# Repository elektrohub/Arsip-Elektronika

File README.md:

# Arsip Elektronika
 
Arsip arsip hobi yang diremajakan ulang (update), disalin ke dalam format Eagle-Cad 7.x, difabrikasi 
[di Elecrow](https://www.elecrow.com)

Semua skematik dan pcb 100% jalan

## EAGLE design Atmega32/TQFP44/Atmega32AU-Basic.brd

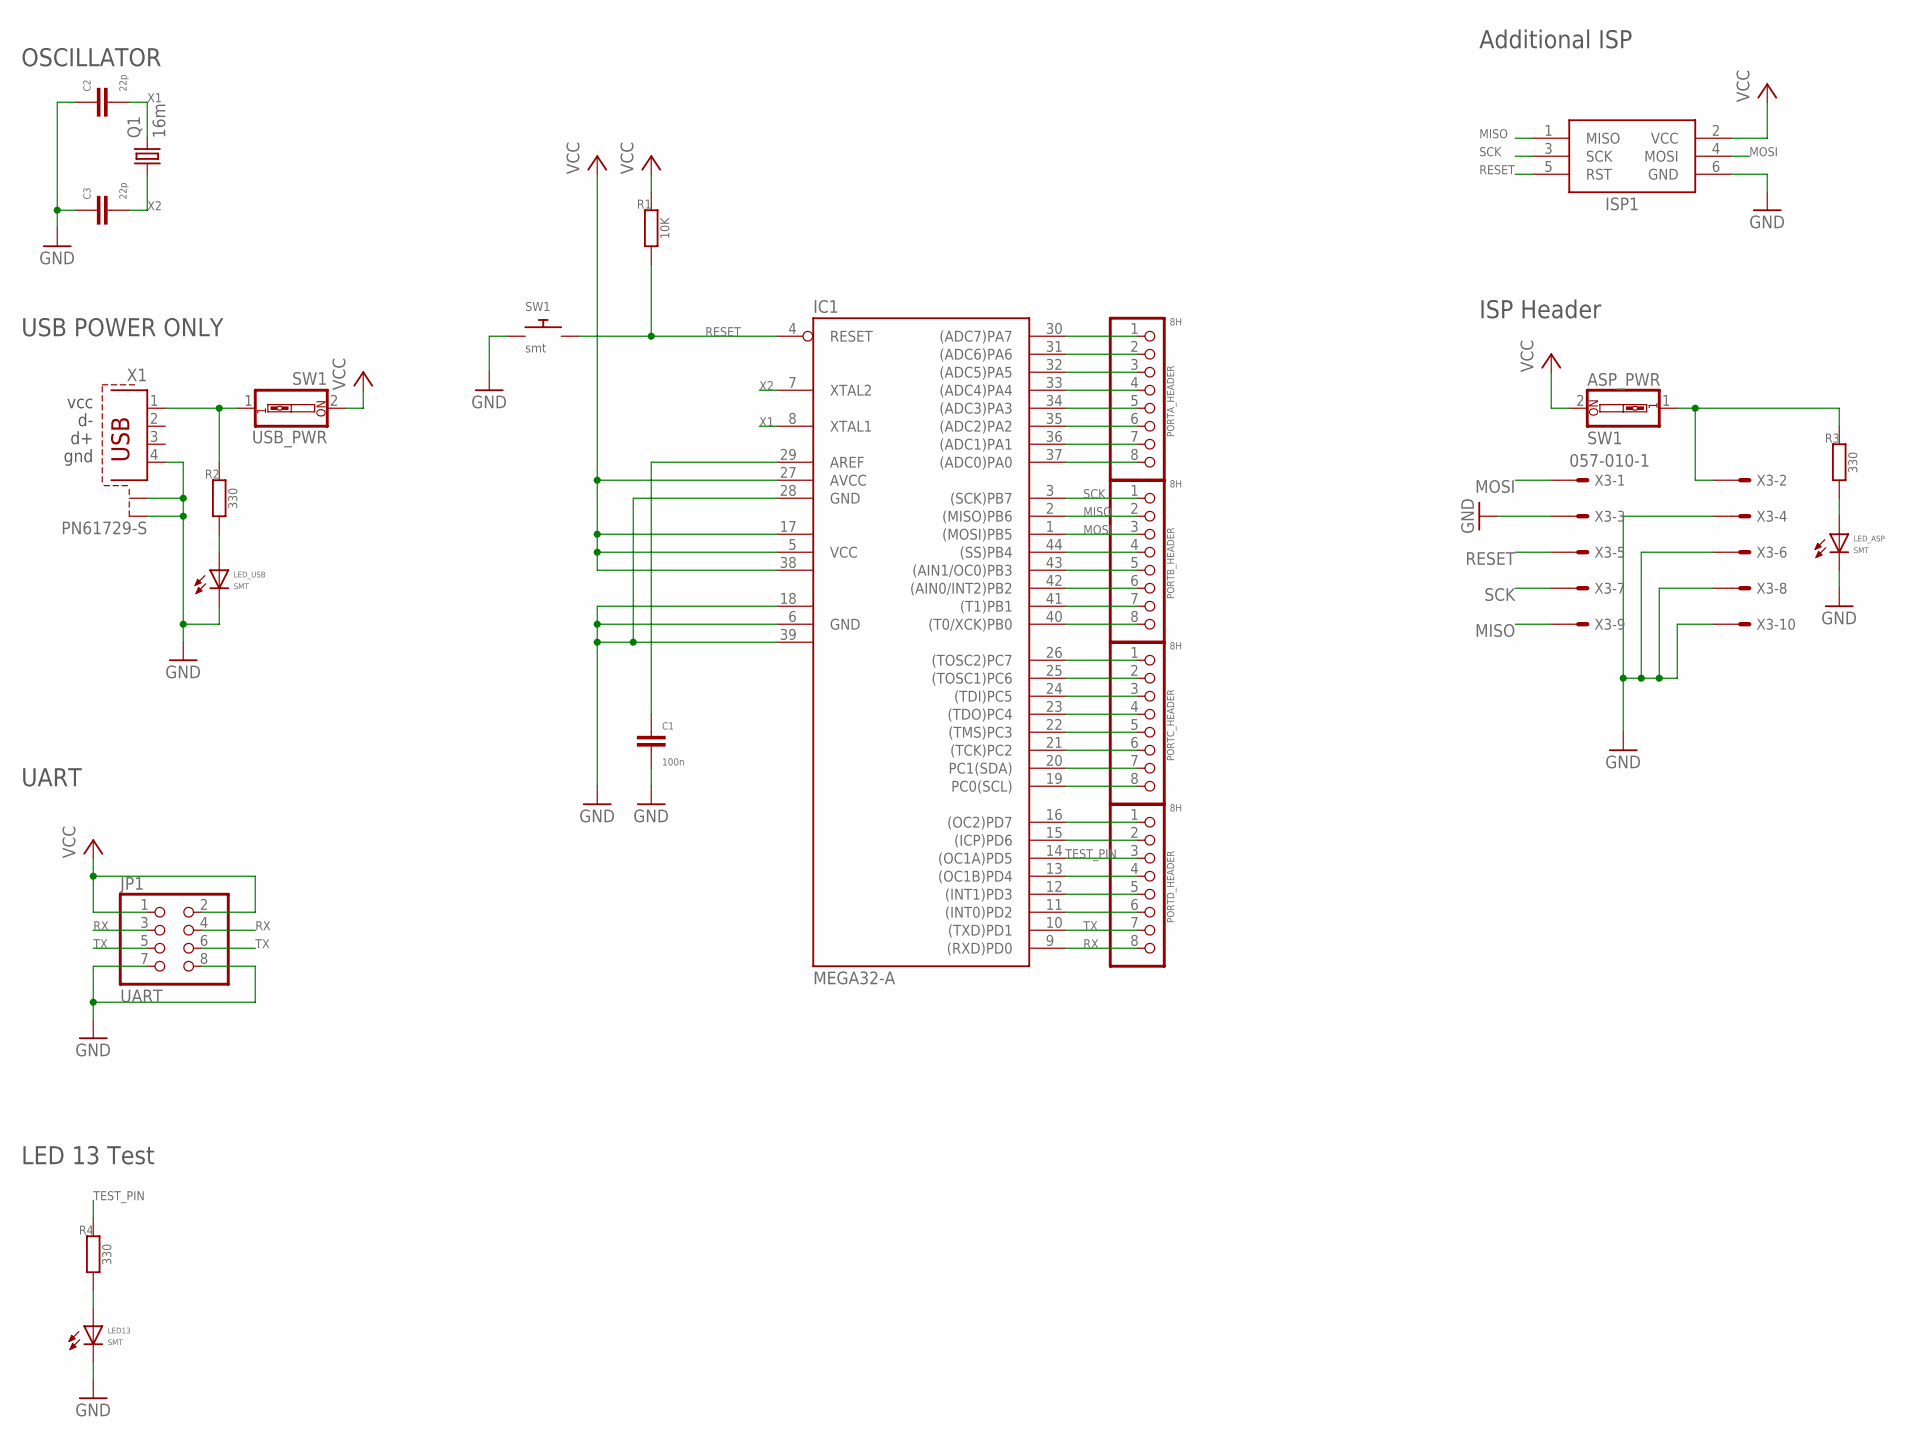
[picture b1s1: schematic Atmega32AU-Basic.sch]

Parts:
ASP_PWR: SW1; EDG-01
C1: 100n; C1206
C2, C3: 22p; C1206
IC1: MEGA32-A; TQFP44
ISP1: AVRISP-6; AVRISP
JP1: UART; 2X04
LED13: SMT; 1206
LED_ASP: SMT; 1206
LED_USB: SMT; 1206
PORTA_HEADER: 8H; 1X08-BIG
PORTB_HEADER: 8H; 1X08-BIG
PORTC_HEADER: 8H; 1X08-BIG
PORTD_HEADER: 8H; 1X08-BIG
Q1: 16m; HC49UP
R1: 10K; M1206
R2, R3, R4: 330; M1206
SW1: smt; TACT_PANA-EVQ
USB_PWR: SW1; EDG-01
X1: PN61729-S
X3: 057-010-1

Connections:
GND: C1.2, C2.1, C3.1, IC1.6 (GND), IC1.18 (GND1), IC1.28 (GND), IC1.39 (GND2), ISP1.6 (GND), JP1.7, JP1.8, LED13.C, LED_ASP.C, LED_USB.C, SW1.P$1, X1.4, X1.S1, X1.S2, X3.3, X3.4, X3.6, X3.8, X3.10
MISO: IC1.2 ((MISO)PB6), ISP1.1 (MISO), PORTB_HEADER.2, X3.9
MOSI: IC1.1 ((MOSI)PB5), ISP1.4 (MOSI), PORTB_HEADER.3, X3.1
unnamed: C1.1, IC1.29 (AREF)
unnamed: IC1.30 ((ADC7)PA7), PORTA_HEADER.1
unnamed: IC1.31 ((ADC6)PA6), PORTA_HEADER.2
unnamed: IC1.32 ((ADC5)PA5), PORTA_HEADER.3
unnamed: IC1.33 ((ADC4)PA4), PORTA_HEADER.4
unnamed: IC1.34 ((ADC3)PA3), PORTA_HEADER.5
unnamed: IC1.35 ((ADC2)PA2), PORTA_HEADER.6
unnamed: IC1.36 ((ADC1)PA1), PORTA_HEADER.7
unnamed: R2.2, USB_PWR.1, X1.1
unnamed: ASP_PWR.1, R3.2, X3.2
unnamed: LED_USB.A, R2.1
unnamed: LED13.A, R4.1
unnamed: IC1.44 ((SS)PB4), PORTB_HEADER.4
unnamed: IC1.43 ((AIN1/OC0)PB3), PORTB_HEADER.5
unnamed: IC1.42 ((AIN0/INT2)PB2), PORTB_HEADER.6
unnamed: IC1.41 ((T1)PB1), PORTB_HEADER.7
unnamed: LED_ASP.A, R3.1
unnamed: IC1.26 ((TOSC2)PC7), PORTC_HEADER.1
unnamed: IC1.25 ((TOSC1)PC6), PORTC_HEADER.2
unnamed: IC1.24 ((TDI)PC5), PORTC_HEADER.3
unnamed: IC1.23 ((TDO)PC4), PORTC_HEADER.4
unnamed: IC1.22 ((TMS)PC3), PORTC_HEADER.5
unnamed: IC1.21 ((TCK)PC2), PORTC_HEADER.6
unnamed: IC1.20 (PC1(SDA)), PORTC_HEADER.7
unnamed: IC1.16 ((OC2)PD7), PORTD_HEADER.1
unnamed: IC1.15 ((ICP)PD6), PORTD_HEADER.2
unnamed: IC1.13 ((OC1B)PD4), PORTD_HEADER.4
unnamed: IC1.12 ((INT1)PD3), PORTD_HEADER.5
unnamed: IC1.11 ((INT0)PD2), PORTD_HEADER.6
PA0: IC1.37 ((ADC0)PA0), PORTA_HEADER.8
PB0: IC1.40 ((T0/XCK)PB0), PORTB_HEADER.8
RESET: IC1.4 (RESET), ISP1.5 (RST), R1.1, SW1.P$2, X3.5
RX: IC1.9 ((RXD)PD0), JP1.3, JP1.4, PORTD_HEADER.8
SCK: IC1.3 ((SCK)PB7), ISP1.3 (SCK), PORTB_HEADER.1, X3.7
SCL: IC1.19 (PC0(SCL)), PORTC_HEADER.8
TEST_PIN: IC1.14 ((OC1A)PD5), PORTD_HEADER.3, R4.2
TX: IC1.10 ((TXD)PD1), JP1.5, JP1.6, PORTD_HEADER.7
VCC: ASP_PWR.2, IC1.5 (VCC), IC1.17 (VCC1), IC1.27 (AVCC), IC1.38 (VCC2), ISP1.2 (VCC), JP1.1, JP1.2, R1.2, USB_PWR.2
X1: C2.2, IC1.8 (XTAL1), Q1.2
X2: C3.2, IC1.7 (XTAL2), Q1.1

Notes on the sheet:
OSCILLATOR
Additional ISP
vcc
gnd
USB POWER ONLY
UART
ISP Header
LED 13 Test

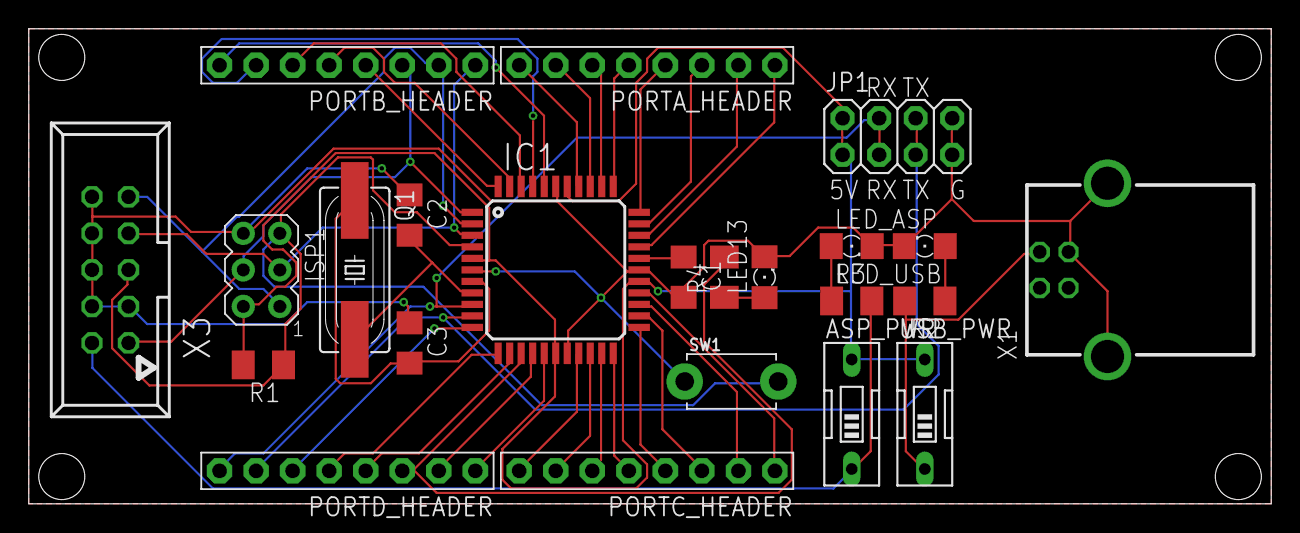
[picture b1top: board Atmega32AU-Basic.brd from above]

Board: 2 copper layers, 86.4 x 33.0 mm, 23 parts (0 on the bottom side), 43 nets.

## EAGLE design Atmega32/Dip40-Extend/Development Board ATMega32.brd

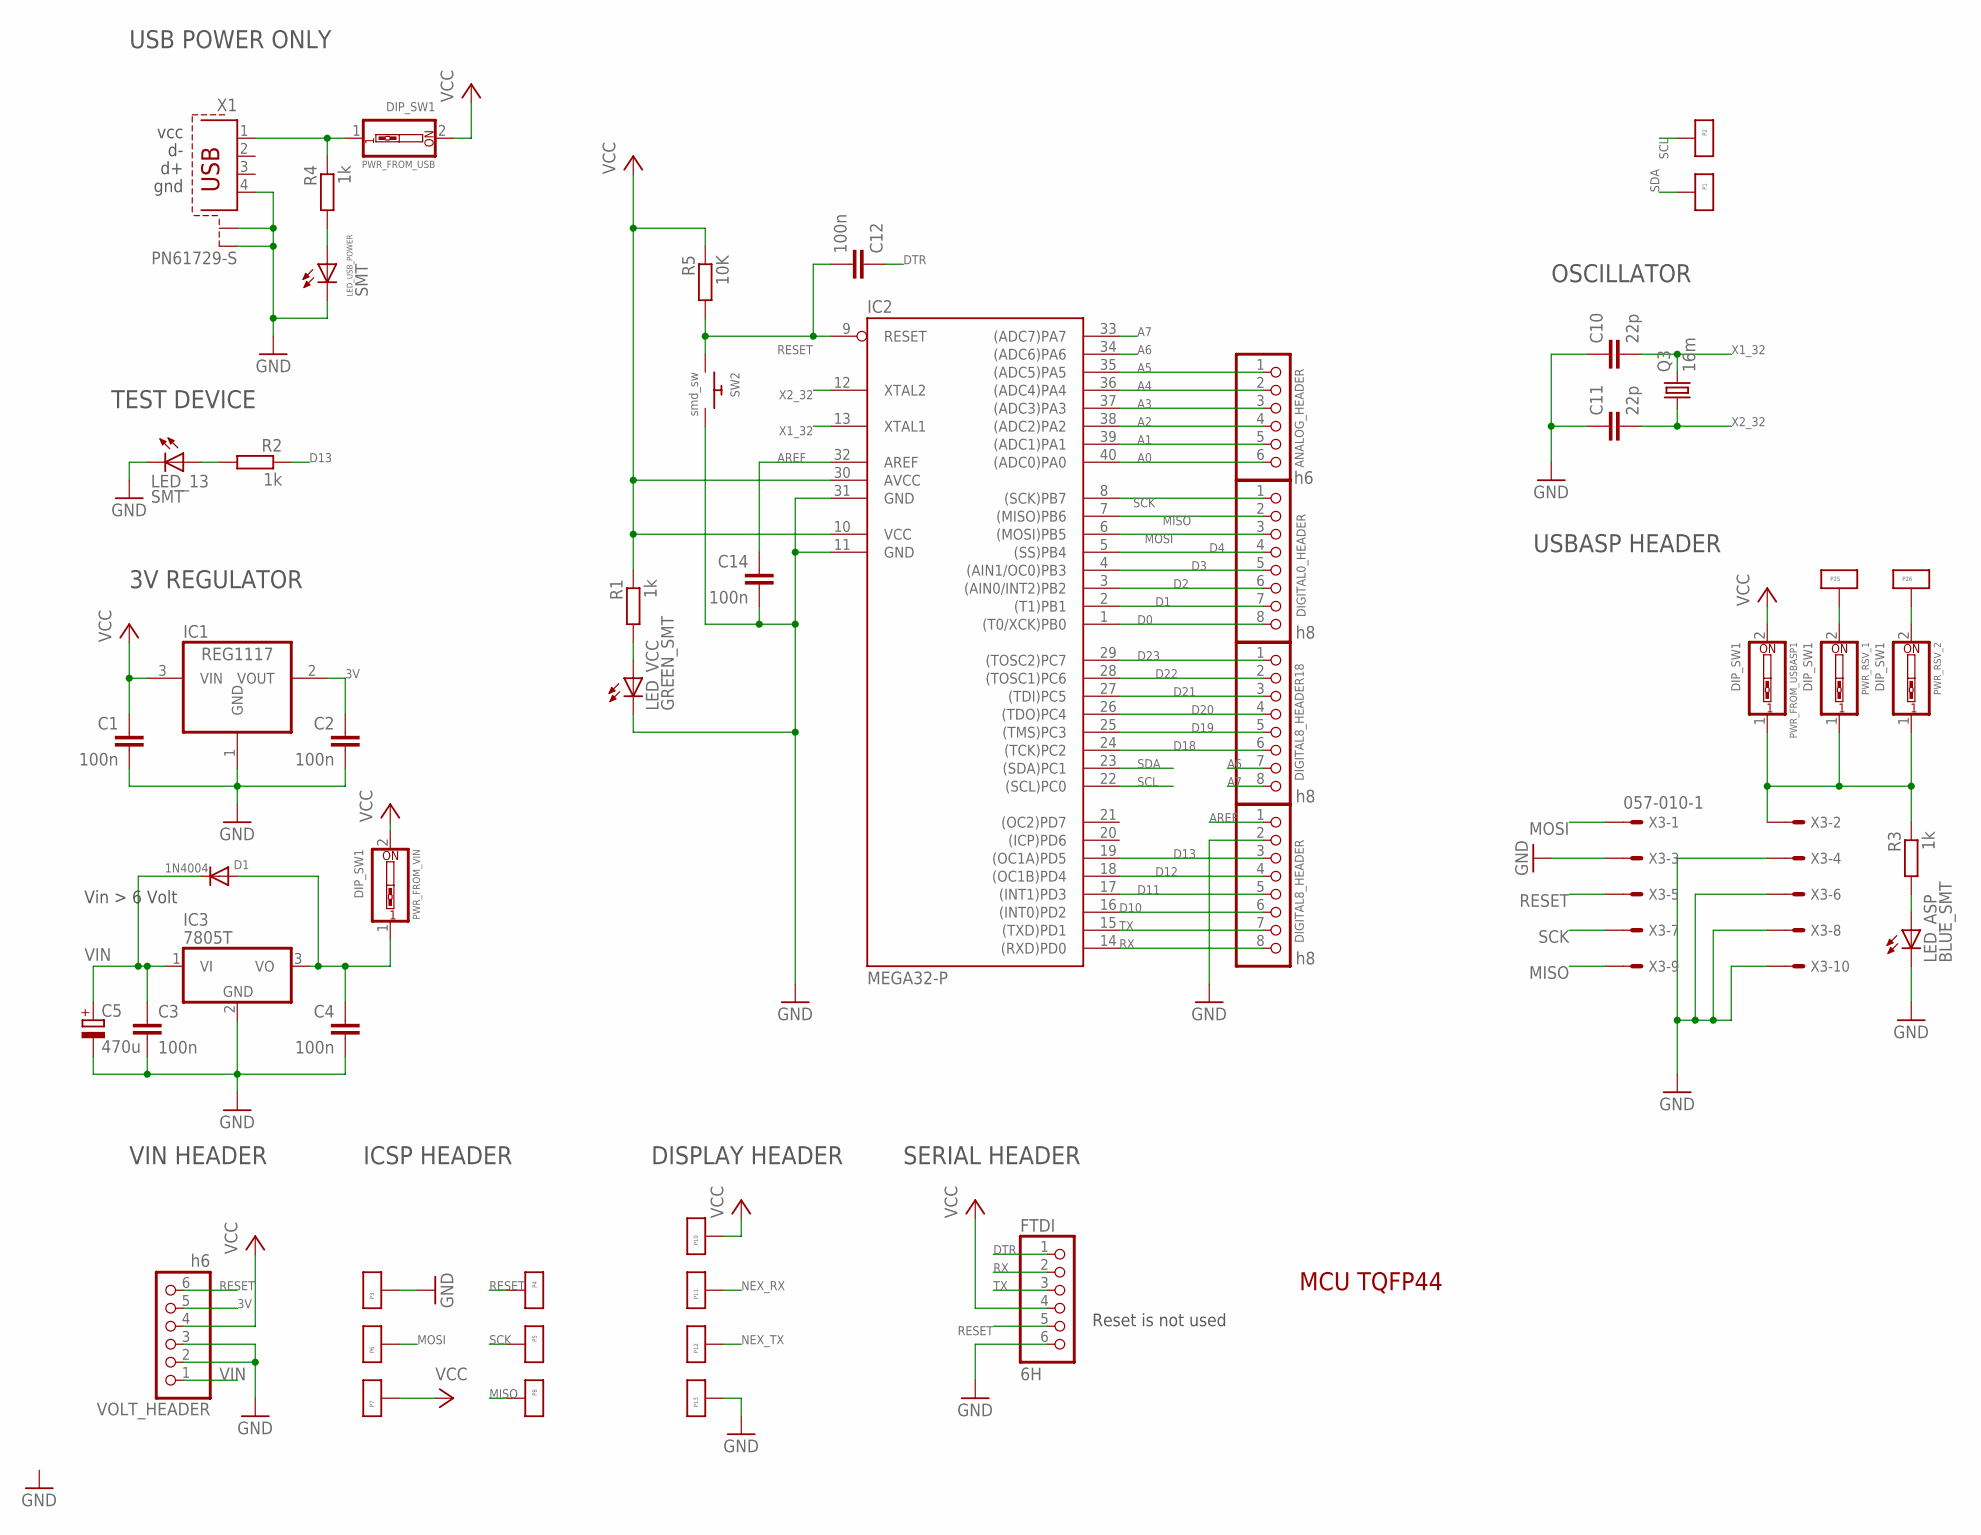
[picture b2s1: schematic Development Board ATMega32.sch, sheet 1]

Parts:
ANALOG_HEADER: h6; 1X06
C1, C2, C12, C14: 100n; C1206
C3, C4: 100n; C050-025X075
C5: 470u; E5-5
C10, C11: 22p; C1206
D1: 1N4004; DO41-10
DIGITAL0_HEADER, DIGITAL8_HEADER, DIGITAL8_HEADER18: h8; 1X08-BIG
FTDI: 6H; 1X06
IC1: REG1117; SOT223
IC2: MEGA32-P; DIL40
IC3: 7805T; TO220H
LED_13: SMT; 1206
LED_ASP: BLUE_SMT; 1206
LED_USB_POWER: SMT; 1206
LED_VCC: GREEN_SMT; 1206
P1, P2, P3, P4, P5, P6, P7, P8, P10, P11, P12, P13, P25, P26: PIN-BIG1X; PIN-BIG
PWR_FROM_USB: DIP_SW1; EDG-01
PWR_FROM_USBASP1: DIP_SW1; EDG-01
PWR_FROM_VIN: DIP_SW1; EDG-01
PWR_RSV_1, PWR_RSV_2: DIP_SW1; EDG-01
Q3: 16m; HC49UP
R1, R2, R3, R4: 1k; R1206
R5: 10K; R1206
SW2: smd_sw; TACT_PANA-EVQ
VOLT_HEADER: h6; 1X06
X1: PN61729-S
X3: 057-010-1

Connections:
3V: C2.1, IC1.2 (VOUT), VOLT_HEADER.5
A0: ANALOG_HEADER.6, IC2.40 ((ADC0)PA0)
A1: ANALOG_HEADER.5, IC2.39 ((ADC1)PA1)
A2: ANALOG_HEADER.4, IC2.38 ((ADC2)PA2)
A3: ANALOG_HEADER.3, IC2.37 ((ADC3)PA3)
A4: ANALOG_HEADER.2, IC2.36 ((ADC4)PA4)
A5: ANALOG_HEADER.1, IC2.35 ((ADC5)PA5)
A6: DIGITAL8_HEADER18.7, IC2.34 ((ADC6)PA6)
A7: DIGITAL8_HEADER18.8, IC2.33 ((ADC7)PA7)
AREF: C14.1, DIGITAL8_HEADER.1, IC2.32 (AREF)
D0: DIGITAL0_HEADER.8, IC2.1 ((T0/XCK)PB0)
D1: DIGITAL0_HEADER.7, IC2.2 ((T1)PB1)
D2: DIGITAL0_HEADER.6, IC2.3 ((AIN0/INT2)PB2)
D3: DIGITAL0_HEADER.5, IC2.4 ((AIN1/OC0)PB3)
D4: DIGITAL0_HEADER.4, IC2.5 ((SS)PB4)
D10: DIGITAL8_HEADER.6, IC2.16 ((INT0)PD2)
D11: DIGITAL8_HEADER.5, IC2.17 ((INT1)PD3)
D12: DIGITAL8_HEADER.4, IC2.18 ((OC1B)PD4)
D13: DIGITAL8_HEADER.3, IC2.19 ((OC1A)PD5), R2.1
D18: DIGITAL8_HEADER18.6, IC2.24 ((TCK)PC2)
D19: DIGITAL8_HEADER18.5, IC2.25 ((TMS)PC3)
D20: DIGITAL8_HEADER18.4, IC2.26 ((TDO)PC4)
D21: DIGITAL8_HEADER18.3, IC2.27 ((TDI)PC5)
D22: DIGITAL8_HEADER18.2, IC2.28 ((TOSC1)PC6)
D23: DIGITAL8_HEADER18.1, IC2.29 ((TOSC2)PC7)
DTR: C12.1, FTDI.1
GND: C1.2, C2.2, C3.2, C4.2, C5.-, C10.1, C11.1, C14.2, DIGITAL8_HEADER.2, FTDI.6, IC1.1 (GND), IC2.11 (GND), IC2.31 (GND), IC3.2 (GND), LED_13.C, LED_ASP.C, LED_USB_POWER.C, LED_VCC.C, P3.P$1, P13.P$1, SW2.P$2, VOLT_HEADER.2, VOLT_HEADER.3, X1.4, X1.S1, X1.S2, X3.3, X3.4, X3.6, X3.8, X3.10; also elsewhere on the board
MISO: DIGITAL0_HEADER.2, IC2.7 ((MISO)PB6), P8.P$1, X3.9
MOSI: DIGITAL0_HEADER.3, IC2.6 ((MOSI)PB5), P6.P$1, X3.1
unnamed: LED_VCC.A, R1.2
unnamed: LED_13.A, R2.2
unnamed: LED_ASP.A, R3.2
unnamed: PWR_FROM_USB.1, R4.1, X1.1
unnamed: LED_USB_POWER.A, R4.2
unnamed: C4.1, D1.A, IC3.3 (VO), PWR_FROM_VIN.1
unnamed: PWR_FROM_USBASP1.1, PWR_RSV_1.1, PWR_RSV_2.1, R3.1, X3.2
NEX_RX: P11.P$1; also elsewhere on the board
NEX_TX: P12.P$1; also elsewhere on the board
RESET: C12.2, FTDI.5, IC2.9 (RESET), P4.P$1, R5.2, SW2.P$1, VOLT_HEADER.6, X3.5
RSV1: P25.P$1, PWR_RSV_1.2
RSV2: P26.P$1, PWR_RSV_2.2
RX: DIGITAL8_HEADER.8, FTDI.2, IC2.14 ((RXD)PD0)
SCK: DIGITAL0_HEADER.1, IC2.8 ((SCK)PB7), P5.P$1, X3.7
SCL: IC2.22 ((SCL)PC0), P2.P$1
SDA: IC2.23 ((SDA)PC1), P1.P$1
TX: DIGITAL8_HEADER.7, FTDI.3, IC2.15 ((TXD)PD1)
VCC: C1.1, FTDI.4, IC1.3 (VIN), IC2.10 (VCC), IC2.30 (AVCC), P7.P$1, P10.P$1, PWR_FROM_USB.2, PWR_FROM_USBASP1.2, PWR_FROM_VIN.2, R1.1, R5.1, VOLT_HEADER.4; also elsewhere on the board
VIN: C3.1, C5.+, D1.C, IC3.1 (VI), VOLT_HEADER.1
X1_32: C10.2, IC2.13 (XTAL1), Q3.2
X2_32: C11.2, IC2.12 (XTAL2), Q3.1

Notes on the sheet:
MCU TQFP44
OSCILLATOR
VIN HEADER
ICSP HEADER
DISPLAY HEADER
USBASP HEADER
3V REGULATOR
TEST DEVICE
SERIAL HEADER
vcc
gnd
USB POWER ONLY
Reset is not used
Vin > 6 Volt

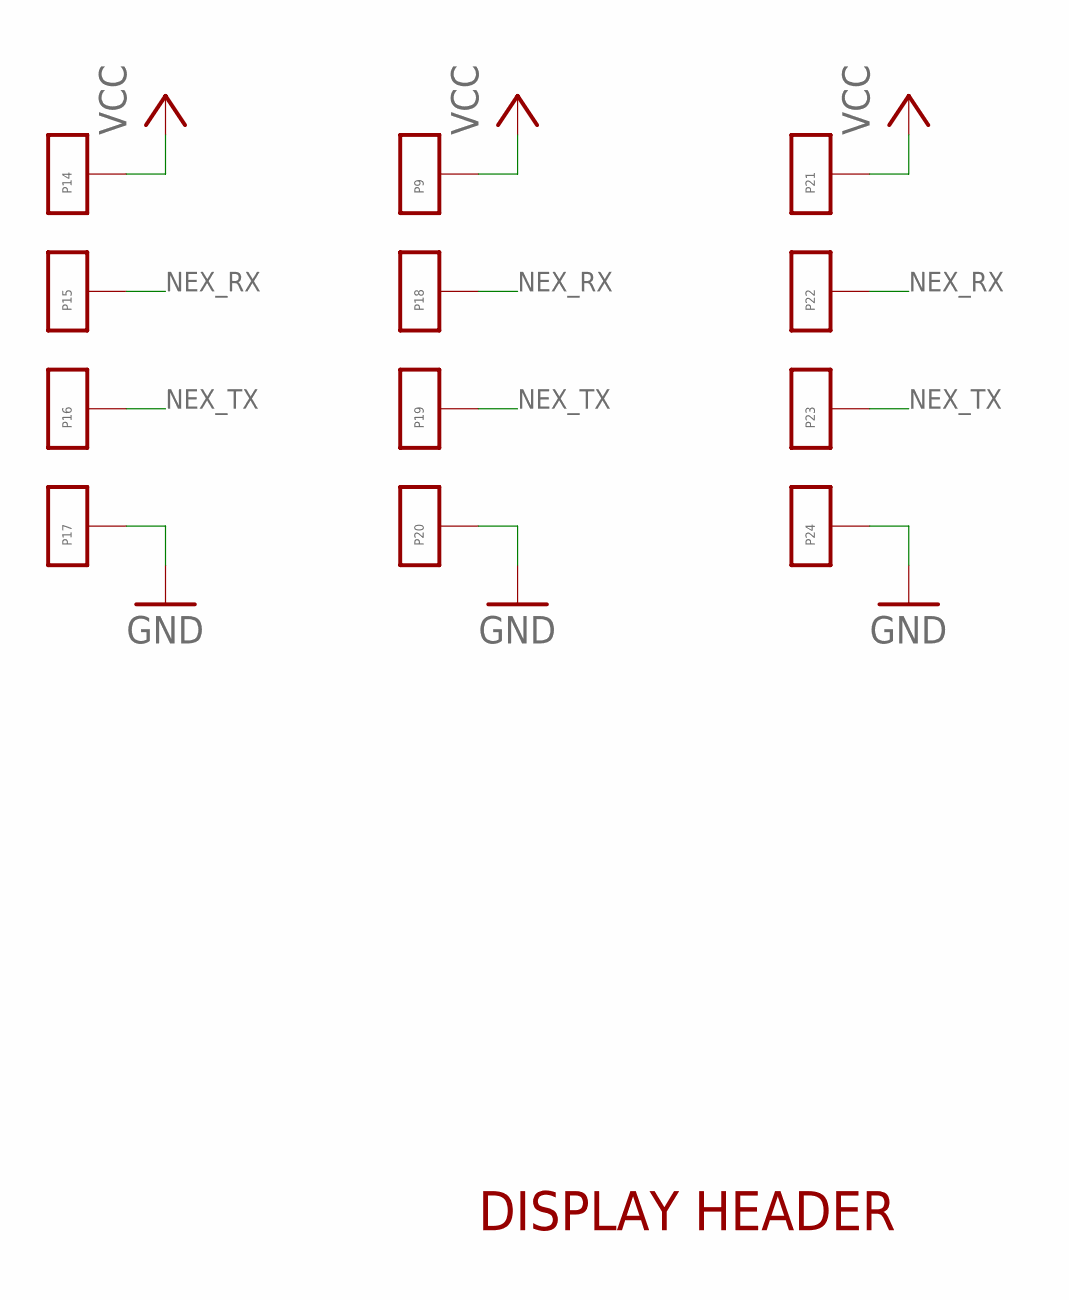
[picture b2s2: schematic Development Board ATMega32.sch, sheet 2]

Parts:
P9, P14, P15, P16, P17, P18, P19, P20, P21, P22, P23, P24: PIN-BIG1X; PIN-BIG

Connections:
GND: P17.P$1, P20.P$1, P24.P$1; also elsewhere on the board
NEX_RX: P15.P$1, P18.P$1, P22.P$1; also elsewhere on the board
NEX_TX: P16.P$1, P19.P$1, P23.P$1; also elsewhere on the board
VCC: P9.P$1, P14.P$1, P21.P$1; also elsewhere on the board

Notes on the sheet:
DISPLAY HEADER

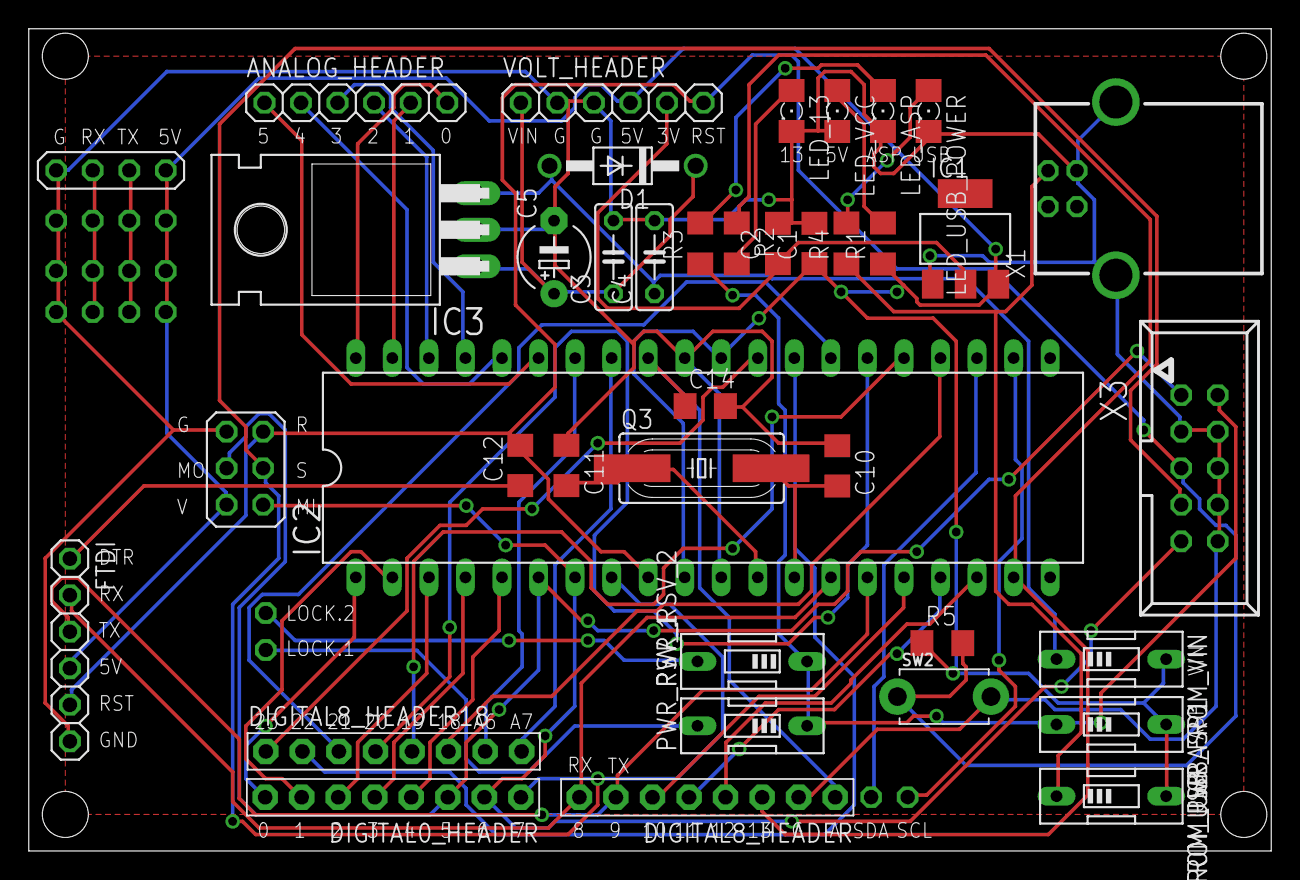
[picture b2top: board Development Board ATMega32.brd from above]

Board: 2 copper layers, 86.4 x 57.1 mm, 63 parts (0 on the bottom side), 50 nets.

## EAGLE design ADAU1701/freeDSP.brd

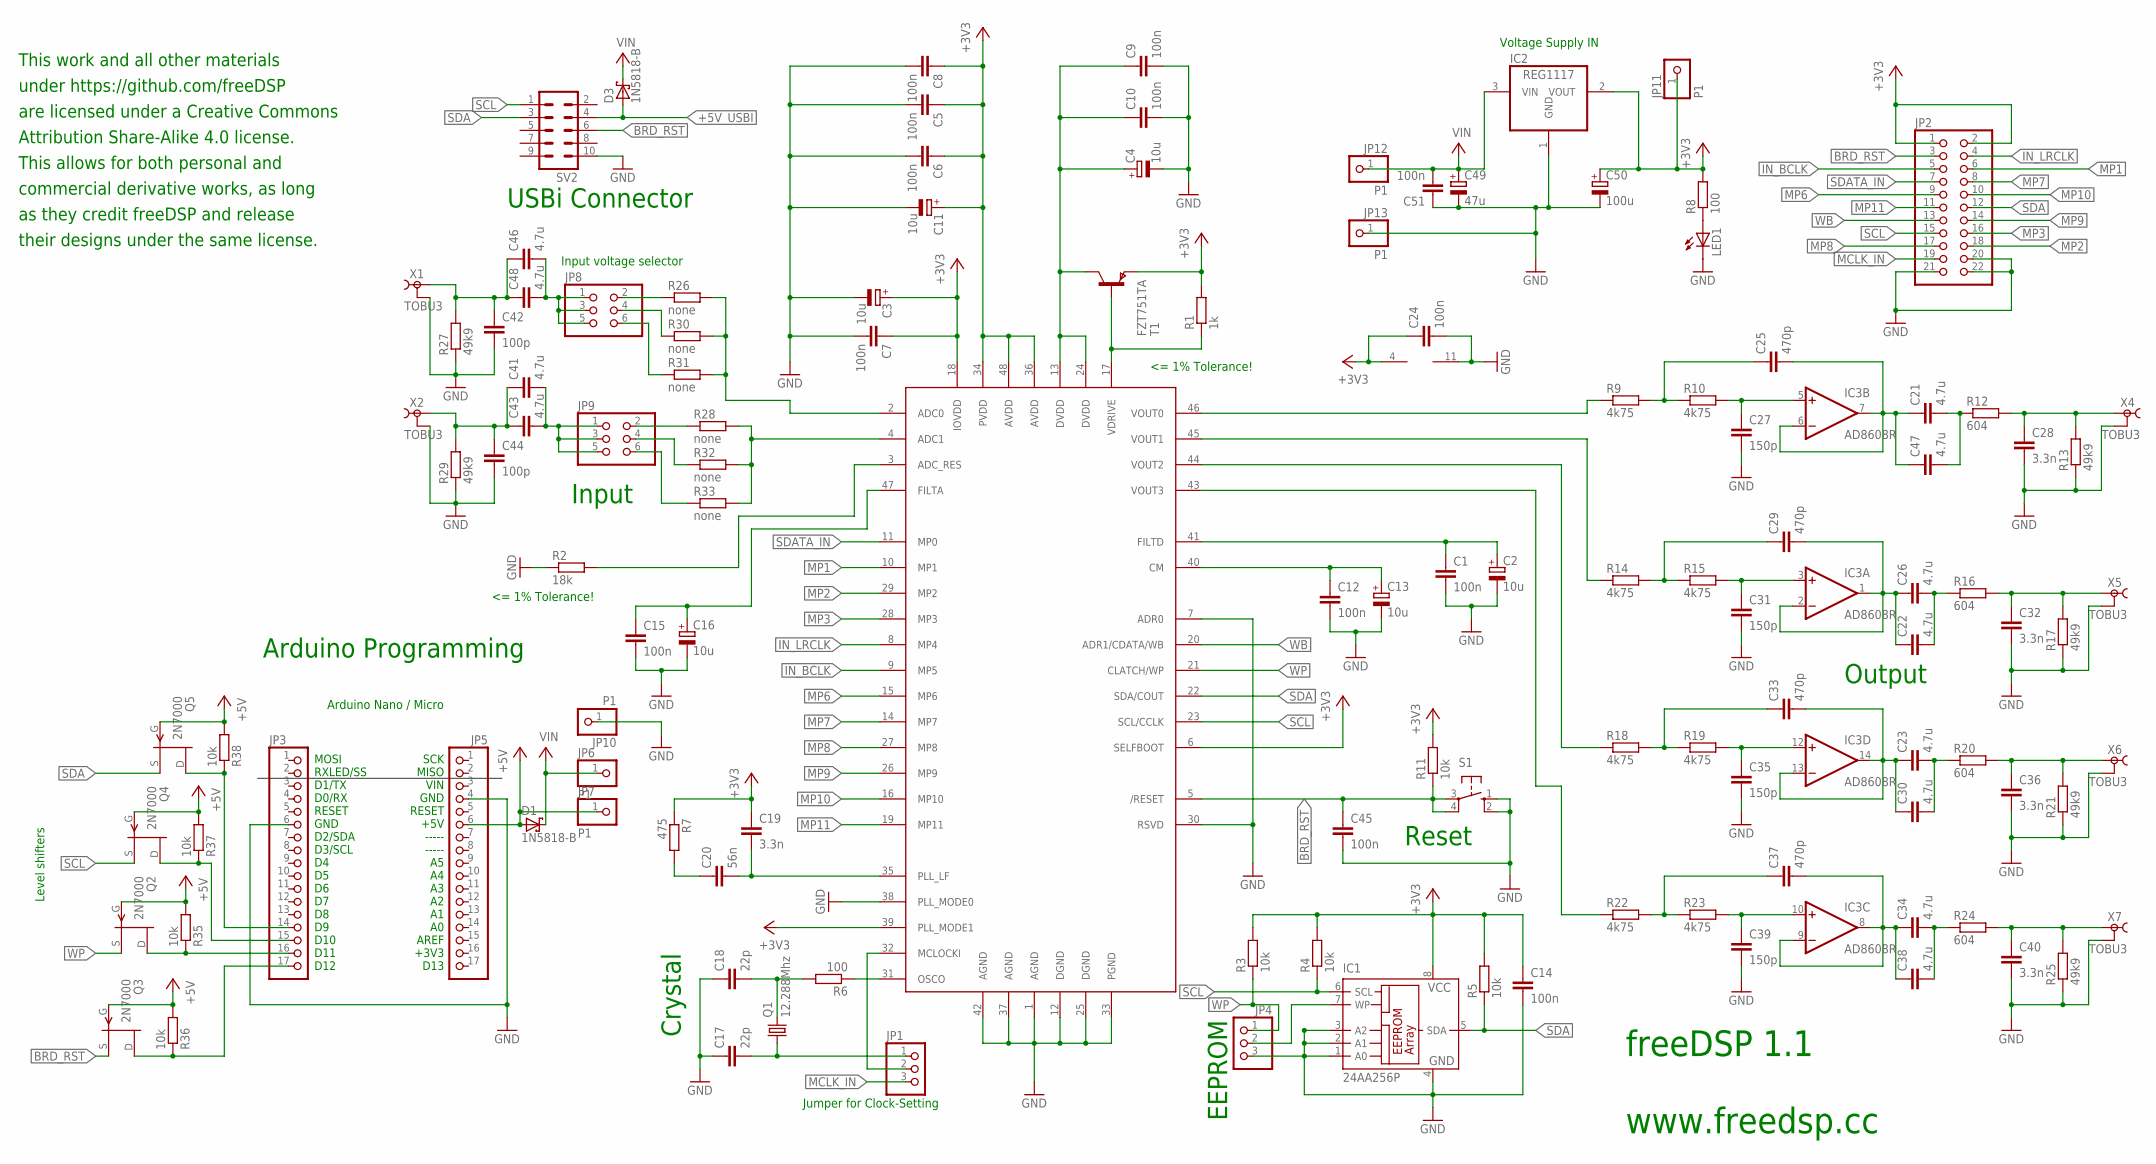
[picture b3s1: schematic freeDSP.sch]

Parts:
C1, C5, C6, C7, C8, C9, C10, C12, C14, C15, C24, C45, C51: 100n; C050-025X075
C2, C3, C4, C11, C13, C16: 10u; E1,8-4
C17, C18: 22p; C025-025X050
C19, C28, C32, C36, C40: 3.3n; C050-025X075
C20: 56n; C050-025X075
C21, C22, C23, C26, C30, C34, C38, C41, C43, C46, C47, C48: 4.7u; C025-025X050
C25, C29, C33, C37: 470p; C050-050X075
C27, C31, C35, C39: 150p; C050-050X075
C42, C44: 100p; C025-025X050
C49: 47u; E2,5-6
C50: 100u; E2,5-6
D1, D3: 1N5818-B; DO41-7.6
IC1: 24AA256P; DIL8
IC2: REG1117; SOT223
IC3: AD8608R; SO-14
JP1, JP4: PINHD-1X3; 1X03
JP2: PINHD-2X11; 2X11
JP3, JP5: PINHD-1X17; 1X17
JP6, JP7, JP10, JP11, JP12, JP13: P1; 1X01
JP8, JP9: PINHD-2X3; 2X03
LED1: LED3MM
Q1: 12.288Mhz; SM49
Q2, Q3, Q4, Q5: 2N7000; TO92
R1: 1k; 0204/7
R2: 18k; 0204/7
R3, R4, R5, R11, R35, R36, R37, R38: 10k; 0204/7
R6, R8: 100; 0204/7
R7: 475; 0204/7
R9, R10, R14, R15, R18, R19, R22, R23: 4k75; 0204/7
R12, R16, R20, R24: 604; 0204/7
R13, R17, R21, R25, R27, R29: 49k9; 0204/7
R26, R28, R30, R31, R32, R33: none; 0204/7
S1: 10-XX; B3F-10XX
SV2: ML10
T1: FZT751TA; SOT223
U$1: ADAU1701; LQFP-48
X1, X2, X4, X5, X6, X7: TOBU3

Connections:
1V8: C4.+, C9.1, C10.1, T1.2 (C), T1.4 (C), U$1.13 (DVDD), U$1.24 (DVDD)
+3V3: C3.+, C5.1, C6.1, C7.1, C8.1, C11.+, C14.1, C19.1, C24.1, C50.+, IC1.8 (VCC), IC2.2 (VOUT), IC3.4 (V+), JP2.1, JP2.2, JP11.1, R1.2, R3.2, R4.2, R5.2, R7.1, R8.2, R11.2, T1.3 (E), U$1.6 (SELFBOOT), U$1.18 (IOVDD), U$1.34 (PVDD), U$1.36 (AVDD), U$1.39 (PLL_MODE1), U$1.48 (AVDD)
+5V: D1.A, JP5.6, JP7.1, Q2.2 (G), Q3.2 (G), Q4.2 (G), Q5.2 (G), R35.2, R36.2, R37.2, R38.2
+5V_USBI: D3.A, SV2.4
ADC0: R28.2, R32.2, R33.2, U$1.4 (ADC1)
BRD_RST: C45.1, JP2.3, Q3.3 (S), R11.1, S1.3, S1.4 (P1), SV2.6, U$1.5 (/RESET)
CM: C12.1, C13.+, U$1.40 (CM)
FILTA: C15.1, C16.+, U$1.47 (FILTA)
FILTD: C1.1, C2.+, U$1.41 (FILTD)
FILTOUT0: C28.1, R12.2, R13.2, X4.1
FILTOUT1: C32.1, R16.2, R17.2, X5.1
FILTOUT2: C36.1, R20.2, R21.2, X6.1
FILTOUT3: C40.1, R24.2, R25.2, X7.1
GND: C1.2, C2.-, C3.-, C4.-, C5.2, C6.2, C7.2, C8.2, C9.2, C10.2, C11.-, C12.2, C13.-, C14.2, C15.2, C16.-, C17.1, C18.1, C24.2, C27.2, C28.2, C31.2, C32.2, C35.2, C36.2, C39.2, C40.2, C42.2, C44.2, C45.2, C49.-, C50.-, C51.1, IC1.1 (A0), IC1.2 (A1), IC1.3 (A2), IC1.4 (GND), IC2.1 (GND), IC3.11 (V-), JP2.20, JP2.21, JP2.22, JP3.6, JP4.3, JP5.4, JP10.1, JP13.1, LED1.K (C), R2.1, R13.1, R17.1, R21.1, R25.1, R27.1, R29.1, S1.1 (S), S1.2 (S1), SV2.10, U$1.1 (AGND), U$1.7 (ADR0), U$1.12 (DGND), U$1.25 (DGND), U$1.30 (RSVD), U$1.33 (PGND), U$1.37 (AGND), U$1.38 (PLL_MODE0), U$1.42 (AGND), X1.2, X1.2@1 (2), X1.2@2 (2), X2.2, X2.2@1 (2), X2.2@2 (2), X4.2, X4.2@1 (2), X4.2@2 (2), X5.2, X5.2@1 (2), X5.2@2 (2), X6.2, X6.2@1 (2), X6.2@2 (2), X7.2, X7.2@1 (2), X7.2@2 (2)
IN_BCLK: JP2.5, U$1.9 (MP5)
IN_LRCLK: JP2.4, U$1.8 (MP4)
MCLK_IN: JP1.3, JP2.19
MP1: JP2.6, U$1.10 (MP1)
MP2: JP2.18, U$1.29 (MP2)
MP3: JP2.16, U$1.28 (MP3)
MP6: JP2.9, U$1.15 (MP6)
MP7: JP2.8, U$1.14 (MP7)
MP8: JP2.17, U$1.27 (MP8)
MP9: JP2.14, U$1.26 (MP9)
MP10: JP2.10, U$1.16 (MP10)
MP11: JP2.11, U$1.19 (MP11)
unnamed: R2.2, U$1.3 (ADC_RES)
unnamed: R1.1, T1.1 (B), U$1.17 (VDRIVE)
unnamed: C19.2, C20.2, U$1.35 (PLL_LF)
unnamed: C23.1, C30.1, C33.2, IC3.13 (-IN), IC3.14 (OUT)
unnamed: C20.1, R7.2
unnamed: C18.2, Q1.2, R6.2
unnamed: C17.2, JP1.1, Q1.1
unnamed: R6.1, U$1.31 (OSCO)
unnamed: LED1.A, R8.1
unnamed: JP1.2, U$1.32 (MCLOCKI)
unnamed: JP3.15, Q4.1 (D), R37.1
unnamed: C21.2, C47.2, R12.1
unnamed: C29.1, R14.2, R15.1
unnamed: JP3.14, Q5.1 (D), R38.1
unnamed: C22.1, C26.1, C29.2, IC3.1 (OUT), IC3.2 (-IN)
unnamed: C31.1, IC3.3 (+IN), R15.2
unnamed: C25.1, R9.2, R10.1
unnamed: C21.1, C25.2, C47.1, IC3.6 (-IN), IC3.7 (OUT)
unnamed: C22.2, C26.2, R16.1
unnamed: C27.1, IC3.5 (+IN), R10.2
unnamed: C33.1, R18.2, R19.1
unnamed: C23.2, C30.2, R20.1
unnamed: JP3.16, Q2.1 (D), R35.1
unnamed: C35.1, IC3.12 (+IN), R19.2
unnamed: JP3.17, Q3.1 (D), R36.1
unnamed: C37.1, R22.2, R23.1
unnamed: C34.1, C37.2, C38.1, IC3.8 (OUT), IC3.9 (-IN)
unnamed: C39.1, IC3.10 (+IN), R23.2
unnamed: C34.2, C38.2, R24.1
unnamed: C46.2, C48.2, JP8.1, JP8.3, JP8.5
unnamed: C42.1, C46.1, C48.1, R27.2, X1.1
unnamed: JP8.2, R26.1
unnamed: JP8.4, R30.1
unnamed: C41.1, C43.1, C44.1, R29.2, X2.1
unnamed: JP8.6, R31.1
unnamed: C41.2, C43.2, JP9.1, JP9.3, JP9.5
unnamed: JP9.2, R28.1
unnamed: JP9.4, R32.1
unnamed: JP9.6, R33.1
unnamed: R26.2, R30.2, R31.2, U$1.2 (ADC0)
unnamed: IC1.7 (WP), JP4.2
SCL: IC1.6 (SCL), JP2.15, Q4.3 (S), R4.1, SV2.1, U$1.23 (SCL/CCLK)
SDA: IC1.5 (SDA), JP2.12, Q5.3 (S), R5.1, SV2.3, U$1.22 (SDA/COUT)
SDATA_IN: JP2.7, U$1.11 (MP0)
V+: C49.+, C51.2, D1.C, D3.C, IC2.3 (VIN), JP6.1, JP12.1
VOUT0: R9.1, U$1.46 (VOUT0)
VOUT1: R14.1, U$1.45 (VOUT1)
VOUT2: R18.1, U$1.44 (VOUT2)
VOUT3: R22.1, U$1.43 (VOUT3)
WB: JP2.13, U$1.20 (ADR1/CDATA/WB)
WP: JP4.1, Q2.3 (S), R3.1, U$1.21 (CLATCH/WP)

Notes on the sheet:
<= 1% Tolerance!
EEPROM
Jumper for Clock-Setting
Crystal
Reset
Output
Input
Input voltage selector
USBi Connector
Arduino Programming
Voltage Supply IN
Arduino Nano / Micro
MOSI RXLED/SS D1/TX D0/RX RESET GND D2/SDA D3/SCL D4 D5 D6 D7 D8 D9 D10 D11 D12
SCK MISO VIN GND RESET +5V ----- ----- A5 A4 A3 A2 A1 A0 AREF +3V3 D13
Level shifters
freeDSP 1.1 www.freedsp.cc
This work and all other materials under https://github.com/freeDSP are licensed under a Creative Commons Attribution Share-Alike 4.0 license. This allows for both personal and commercial derivative works, as long as they credit freeDSP and release their designs under the same license.

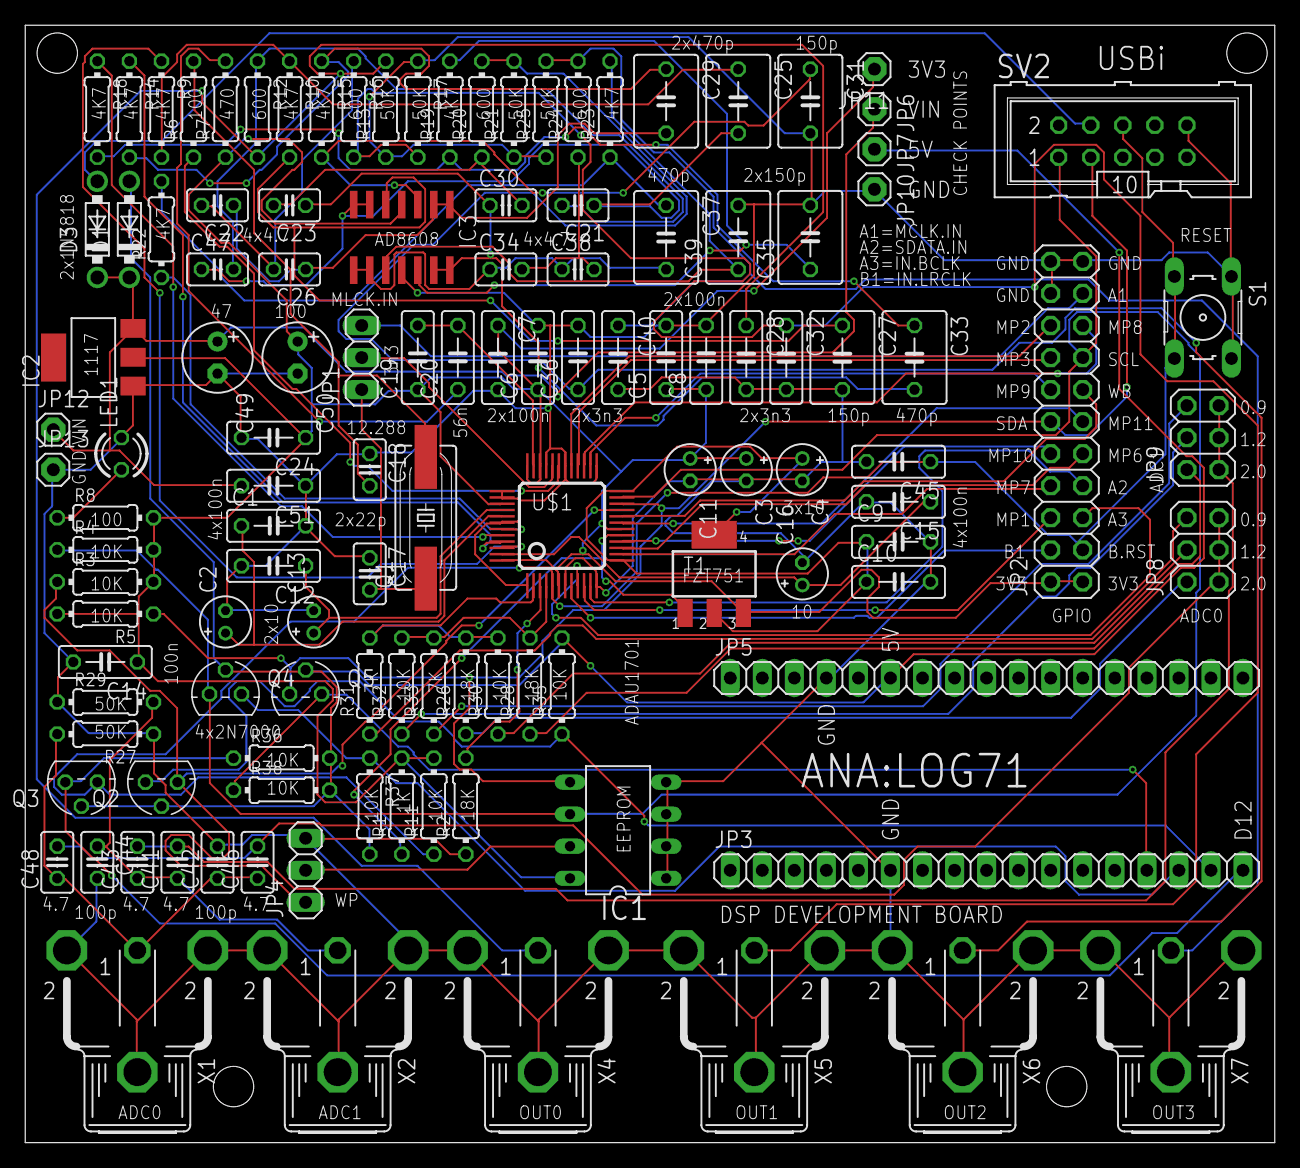
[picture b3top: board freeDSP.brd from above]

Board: 2 copper layers, 99.0 x 88.6 mm, 122 parts (0 on the bottom side), 77 nets.

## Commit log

2019-07-13 Update .gitignore
    Commit Lokal
2019-07-13 Create Template Komponen.sch
    Template Done
2019-07-14 Add LF357 Headphones Amplifier
2019-07-14 Add PSU 15V Rail to Rail
2019-07-14 add OPA4134 Headphones Amplifier
2019-07-14 Add ADAU1701
2019-07-14 Add Elecrow and SparkFun Rules Eagle
2019-07-14 Add Atmega32 DIP40
2019-07-14 Update Atmega32 Dip 40
2019-07-17 Add Komponen Label
2019-07-17 add images
2019-07-17 add pcb image
2019-07-21 add atmega32 extends dip40
2019-07-21 update Atemga32 Extends Dip40
2019-07-21 Add Atmega32AU TQFP44
